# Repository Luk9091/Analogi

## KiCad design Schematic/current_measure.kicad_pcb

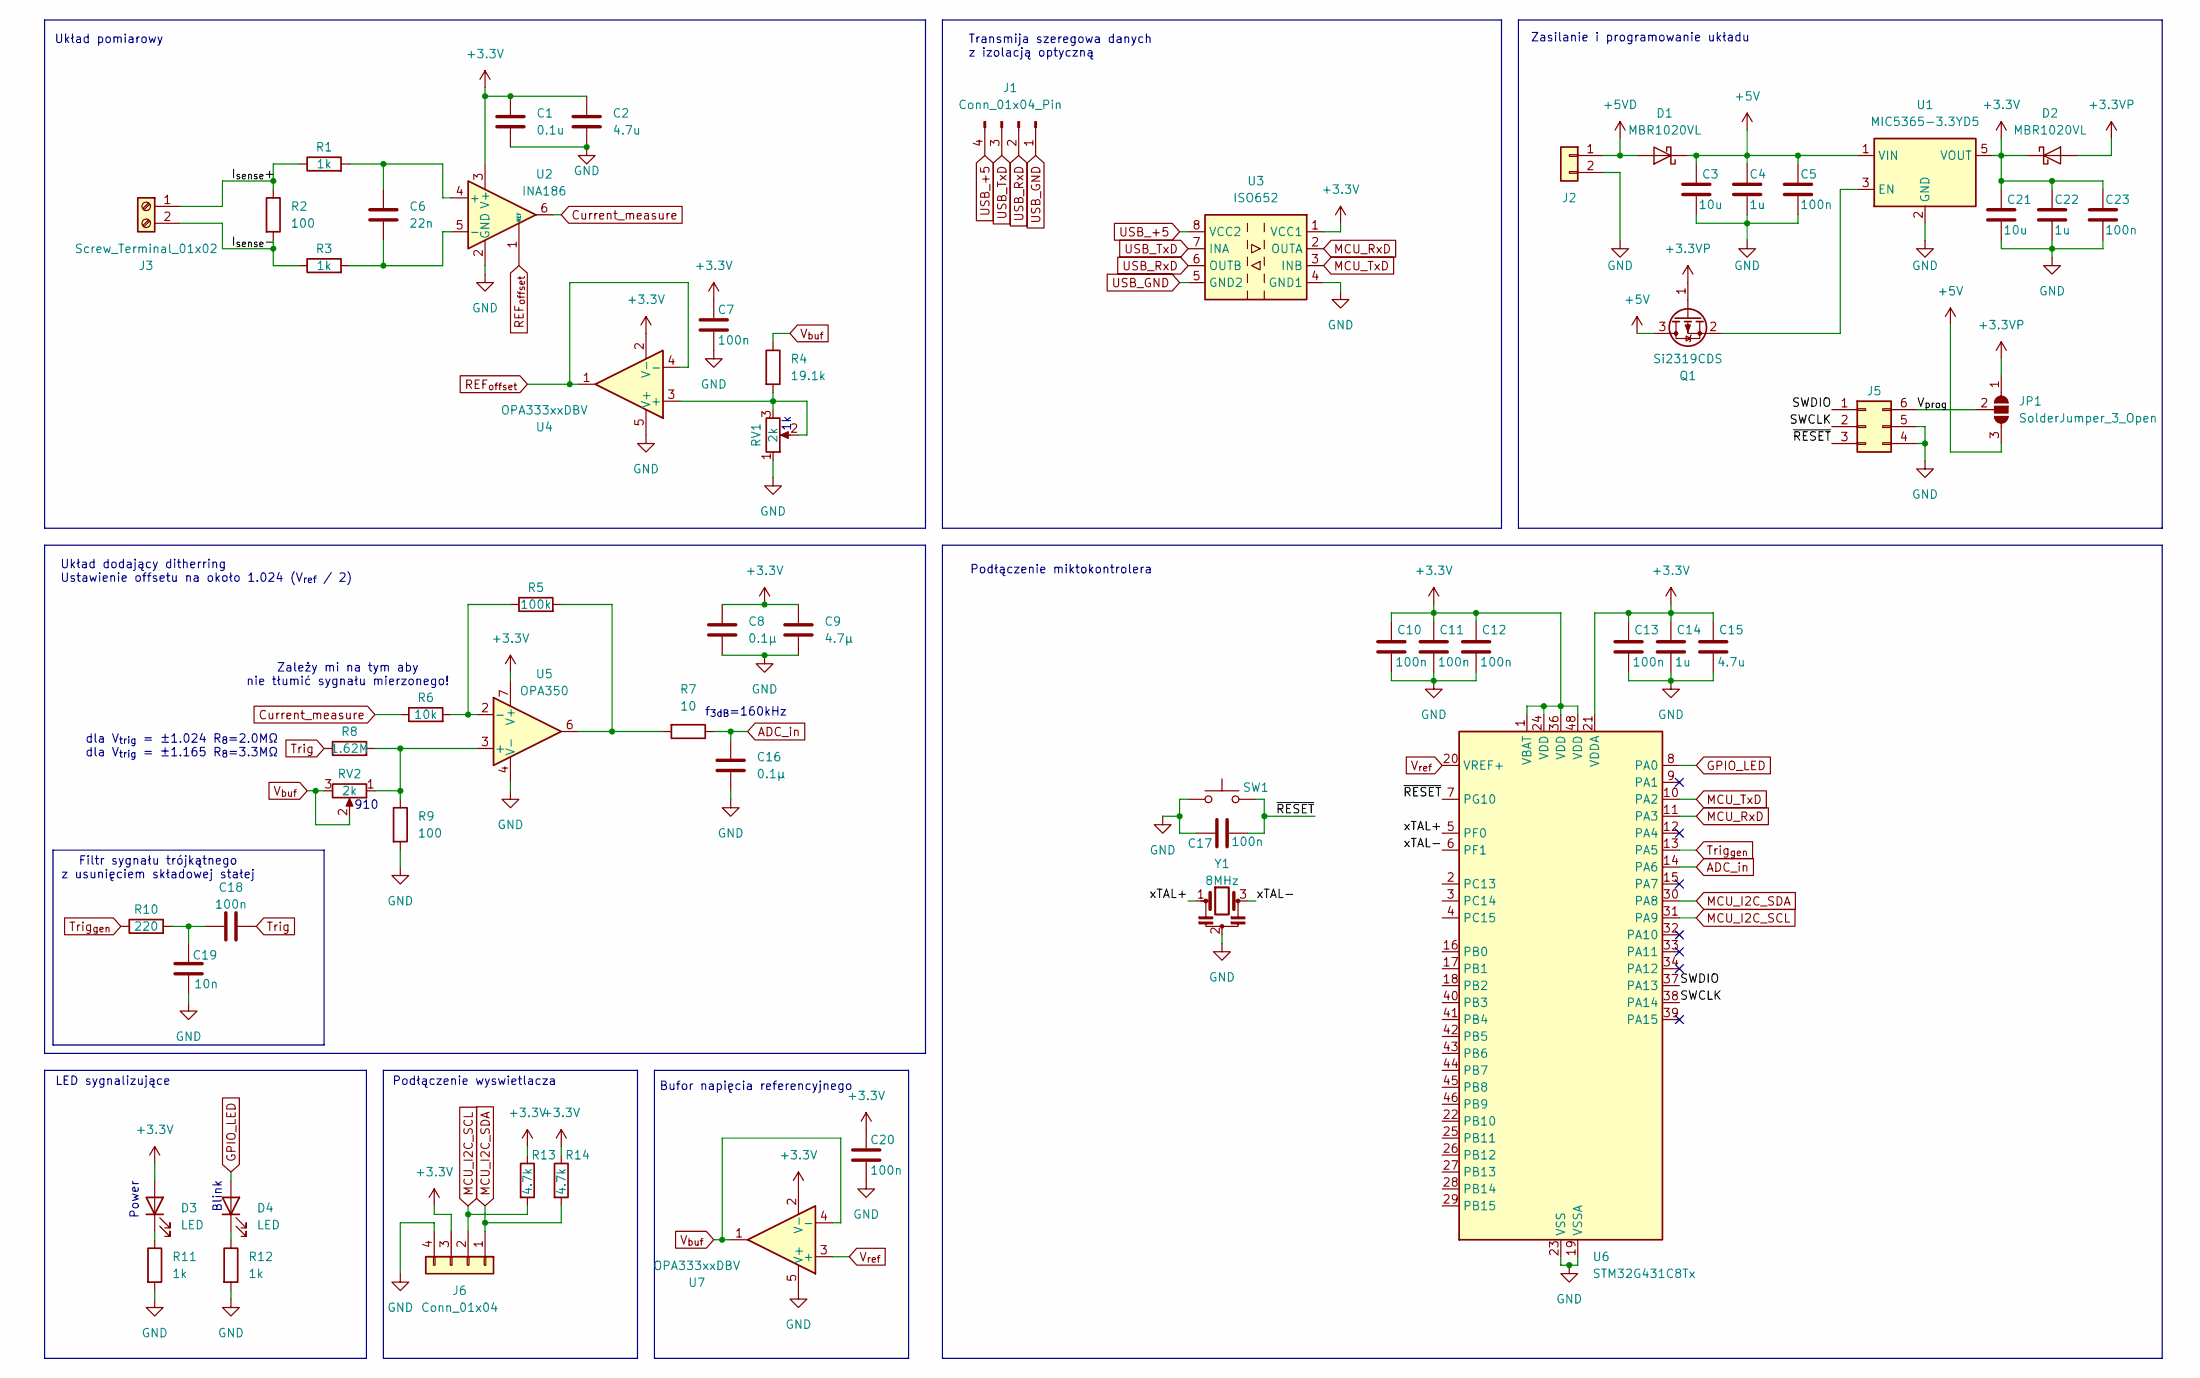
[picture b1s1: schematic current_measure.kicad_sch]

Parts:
C1: 0.1u; C_0805_2012Metric
C2, C15: 4.7u; C_0805_2012Metric
C3, C21: 10u; C_0805_2012Metric
C4, C14, C22: 1u; C_0805_2012Metric
C5, C7, C10, C11, C12, C13, C17, C18, C20, C23: 100n; C_0805_2012Metric
C6: 22n; C_0805_2012Metric
C8, C16: 0.1µ; C_0805_2012Metric
C9: 4.7µ; C_0805_2012Metric
C19: 10n; C_0805_2012Metric
D1, D2: MBR1020VL; D_SOD-123F
D3, D4: LED; LED_0805_2012Metric_Pad1.15x1.40mm_HandSolder
J1: Conn_01x04_Pin; PinHeader_1x04_P2.54mm_Vertical
J2: Conn_01x02; PinHeader_1x02_P2.54mm_Vertical
J3: Screw_Terminal_01x02; TerminalBlock_Xinya_XY308-2.54-2P_1x02_P2.54mm_Horizontal
J5: Conn_02x03_Counter_Clockwise; PinSocket_2x03_P2.54mm_Vertical
J6: Conn_01x04; PinSocket_1x04_P2.54mm_Vertical
JP1: SolderJumper_3_Open; SolderJumper-3_P1.3mm_Open_Pad1.0x1.5mm
Q1: Si2319CDS; SOT-23
R1, R3, R11, R12: 1k; R_0805_2012Metric
R2, R9: 100; R_0805_2012Metric
R4: 19.1k; R_0805_2012Metric
R5: 100k; R_0805_2012Metric
R6: 10k; R_0805_2012Metric
R7: 10; R_0805_2012Metric
R8: 1.62M; R_0805_2012Metric
R10: 220; R_0805_2012Metric
R13, R14: 4.7k; R_0805_2012Metric
RV1, RV2: 2k; Potentiometer_Bourns_3296Z_Horizontal
SW1: SW_Push; SW_SPST_PTS647_Sx38
U1: MIC5365-3.3YD5; TSOT-23-5_HandSoldering
U2: INA186; SOT-363_SC-70-6_Handsoldering
U3: ISO652; SOIC-8_3.9x4.9mm_P1.27mm
U4: OPA333xxDBV; SOT-23-5
U5: OPA350; SOIC-8_3.9x4.9mm_P1.27mm
U6: STM32G431C8Tx; LQFP-48_7x7mm_P0.5mm
U7: OPA333xxDBV; SOT-23-5_HandSoldering
Y1: 8MHz; Resonator_SMD_Murata_CSTxExxV-3Pin_3.0x1.1mm

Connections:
+3.3V: C1.1, C2.1, C7.1, C8.1, C9.1, C10.1, C11.1, C12.1, C13.1, C14.1, C15.1, C20.1, C21.1, C22.1, C23.1, D2.1 (K), D3.2 (A), J6.3, R13.1, R14.1, U1.5 (VOUT), U2.3 (V+), U3.1 (VCC1), U4.2 (V-), U5.7 (V+), U6.1 (VBAT), U6.21 (VDDA), U6.24 (VDD), U6.36 (VDD), U6.48 (VDD), U7.2 (V-)
+3.3VP: D2.2 (A), JP1.1 (A), Q1.1 (G)
+5V: C3.1, C4.1, C5.1, D1.1 (K), JP1.3 (B), Q1.3 (D), U1.1 (VIN)
+5VD: D1.2 (A), J2.1
/I_{sense}+: J3.1, R1.1, R2.1
/I_{sense}-: J3.2, R2.2, R3.1
/SWCLK: J5.2, U6.38 (PA14)
/SWDIO: J5.1, U6.37 (PA13)
/V_{prog}: J5.6, JP1.2 (C)
/xTAL+: U6.5 (PF0), Y1.1
/xTAL-: U6.6 (PF1), Y1.3
/~RESET: C17.1, J5.3, SW1.2, U6.7 (PG10)
ADC_in: C16.1, R7.1, U6.14 (PA6)
Current_measure: R6.1, U2.6
GND: C1.2, C2.2, C3.2, C4.2, C5.2, C7.2, C8.2, C9.2, C10.2, C11.2, C12.2, C13.2, C14.2, C15.2, C16.2, C17.2, C19.2, C20.2, C21.2, C22.2, C23.2, J2.2, J5.4, J5.5, J6.4, R9.2, R11.2, R12.2, RV1.1, SW1.1, U1.2 (GND), U2.2 (GND), U3.4 (GND1), U4.5 (V+), U5.4 (V-), U6.19 (VSSA), U6.23 (VSS), U6.35 (VSS), U6.47 (VSS), U7.5 (V+), Y1.2
GPIO_LED: D4.2 (A), U6.8 (PA0)
MCU_I2C_SCL: J6.2, R13.2, U6.31 (PA9)
MCU_I2C_SDA: J6.1, R14.2, U6.30 (PA8)
MCU_RxD: U3.2 (OUTA), U6.11 (PA3)
MCU_TxD: U3.3 (INB), U6.10 (PA2)
unnamed: C18.1, C19.1, R10.2
unnamed: D3.1 (K), R11.1
unnamed: D4.1 (K), R12.1
unnamed: Q1.2 (S), U1.3 (EN)
unnamed: R5.2, R7.2, U5.6
unnamed: C6.1, R1.2, U2.4 (+)
unnamed: C6.2, R3.2, U2.5 (-)
unnamed: R4.2, RV1.2, RV1.3, U4.3 (+)
unnamed: R8.2, R9.1, RV2.1, U5.3 (+)
unnamed: R5.1, R6.2, U5.2 (-)
REF_{offset}: U2.1 (REF), U4.1, U4.4 (-)
Trig: C18.2, R8.1
Trig_{gen}: R10.1, U6.13 (PA5)
USB_+5: J1.4, U3.8 (VCC2)
USB_GND: J1.1, U3.5 (GND2)
USB_RxD: J1.2, U3.6 (OUTB)
USB_TxD: J1.3, U3.7 (INA)
V_{buf}: R4.1, RV2.2, RV2.3, U7.1, U7.4 (-)
V_{ref}: U6.20 (VREF+), U7.3 (+)

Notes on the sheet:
Podłączenie wyswietlacza
Transmija szeregowa danych z izolacją optyczną
Podłączenie miktokontrolera
Układ pomiarowy
LED sygnalizujące
Zależy mi na tym aby nie tłumić sygnału mierzonego!
910
Filtr sygnału trójkątnego z usunięciem składowej stałej
Bufor napięcia referencyjnego
Zasilanie i programowanie układu
Power
Blink
f_{3dB}=160kHz
Układ dodający ditherring Ustawienie offsetu na około 1.024 (V_{ref} / 2)
dla V_{trig} = ±1.024 R_{8}=2.0MΩ dla V_{trig} = ±1.165 R_{8}=3.3MΩ

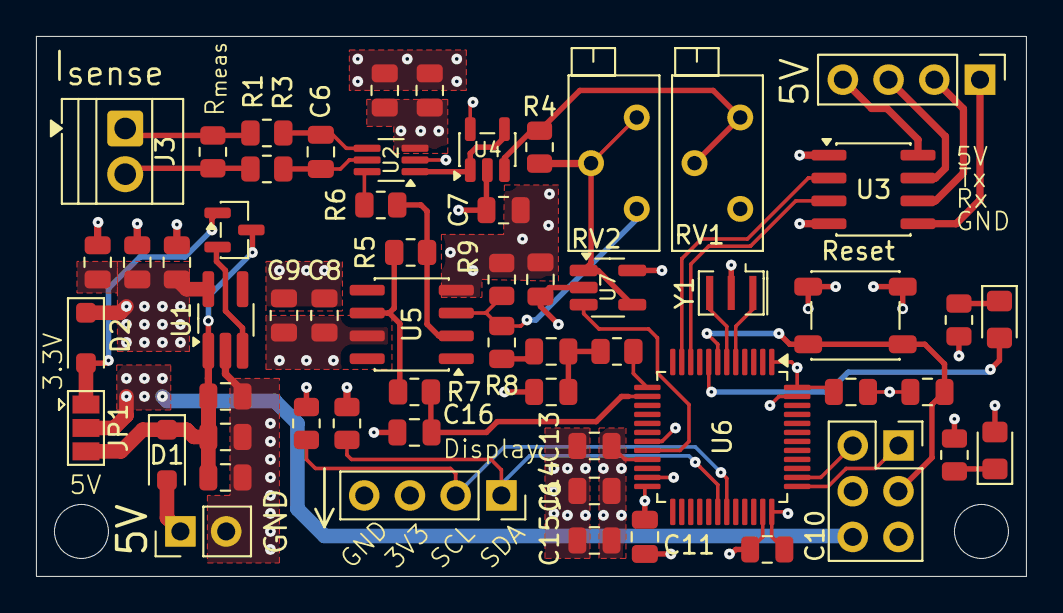
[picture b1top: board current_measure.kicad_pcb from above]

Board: 4 copper layers, 55.0 x 30.0 mm, 59 parts (0 on the bottom side), 39 nets.

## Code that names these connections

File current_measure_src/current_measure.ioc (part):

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Mcu.Name=STM32G431C(6-8-B)Tx
Mcu.Package=LQFP48
Mcu.UserName=STM32G431C6Tx
PA0.GPIOParameters=GPIO_Label
PA0.GPIO_Label=STATE_LED
PA0.Signal=GPIO_Output
PA13.Mode=Serial_Wire
PA13.Signal=SYS_JTMS-SWDIO
PA14.Mode=Serial_Wire
PA14.Signal=SYS_JTCK-SWCLK
PA2.Mode=Asynchronous
PA2.Signal=USART2_TX
PA3.Mode=Asynchronous
PA3.Signal=USART2_RX
PA5.GPIOParameters=GPIO_Label
PA5.GPIO_Label=TRIG
PA5.Signal=COMP_DAC12_group
PA6.Mode=IN3-Single-Ended
PA6.Signal=ADC2_IN3
PA8.Mode=I2C
PA8.Signal=I2C2_SDA
PA9.Mode=I2C
PA9.Signal=I2C2_SCL
PF0-OSC_IN.Mode=HSE-External-Oscillator
PF0-OSC_IN.Signal=RCC_OSC_IN
PF1-OSC_OUT.Mode=HSE-External-Oscillator
PF1-OSC_OUT.Signal=RCC_OSC_OUT
RCC.HSE_VALUE=8000000
RCC.SYSCLKFreq_VALUE=96000000
RCC.SYSCLKSource=RCC_SYSCLKSOURCE_PLLCLK
board=custom

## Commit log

2025-10-15 Init
2025-10-21 Add parameters
2025-10-29 Week 27.10.2025
2025-11-03 Week 03.11.2025
2025-11-03 Update gitignore backup and zip
2025-11-04 Add documentation
2025-11-04 Update schematic
2025-11-04 Clean schematic
2025-11-09 Update simulation
2025-11-11 Changed buffor amplifiers, changed potentiometer, creating layout
2025-11-11 rm cache
2025-11-11 improved layout
2025-11-12 Initial PCB
2025-11-13 PCB small
2025-11-18 Fix small issues with I2C and add power cap
2026-02-01 Firmware update
